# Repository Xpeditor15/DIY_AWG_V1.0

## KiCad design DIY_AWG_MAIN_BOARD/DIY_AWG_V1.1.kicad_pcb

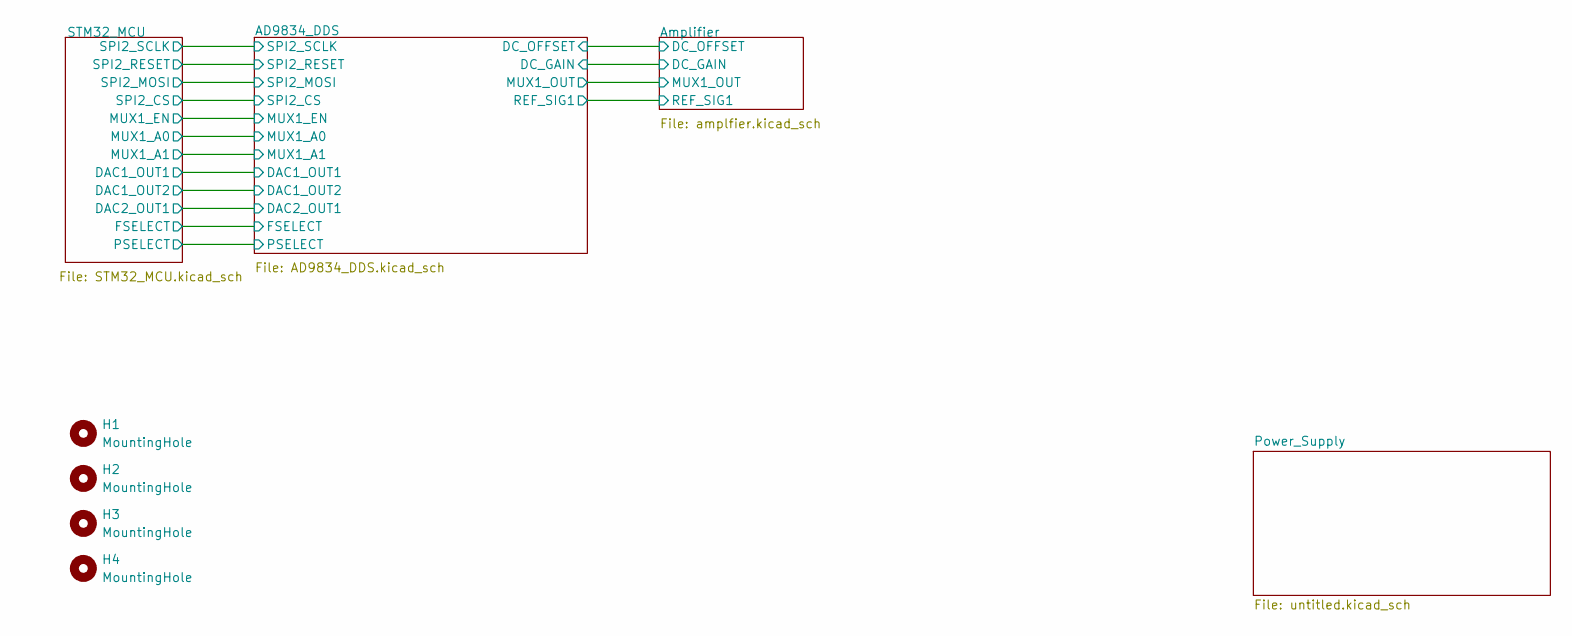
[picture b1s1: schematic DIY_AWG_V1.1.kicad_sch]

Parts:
H1, H2, H3, H4: MountingHole; MountingHole_3.2mm_M3

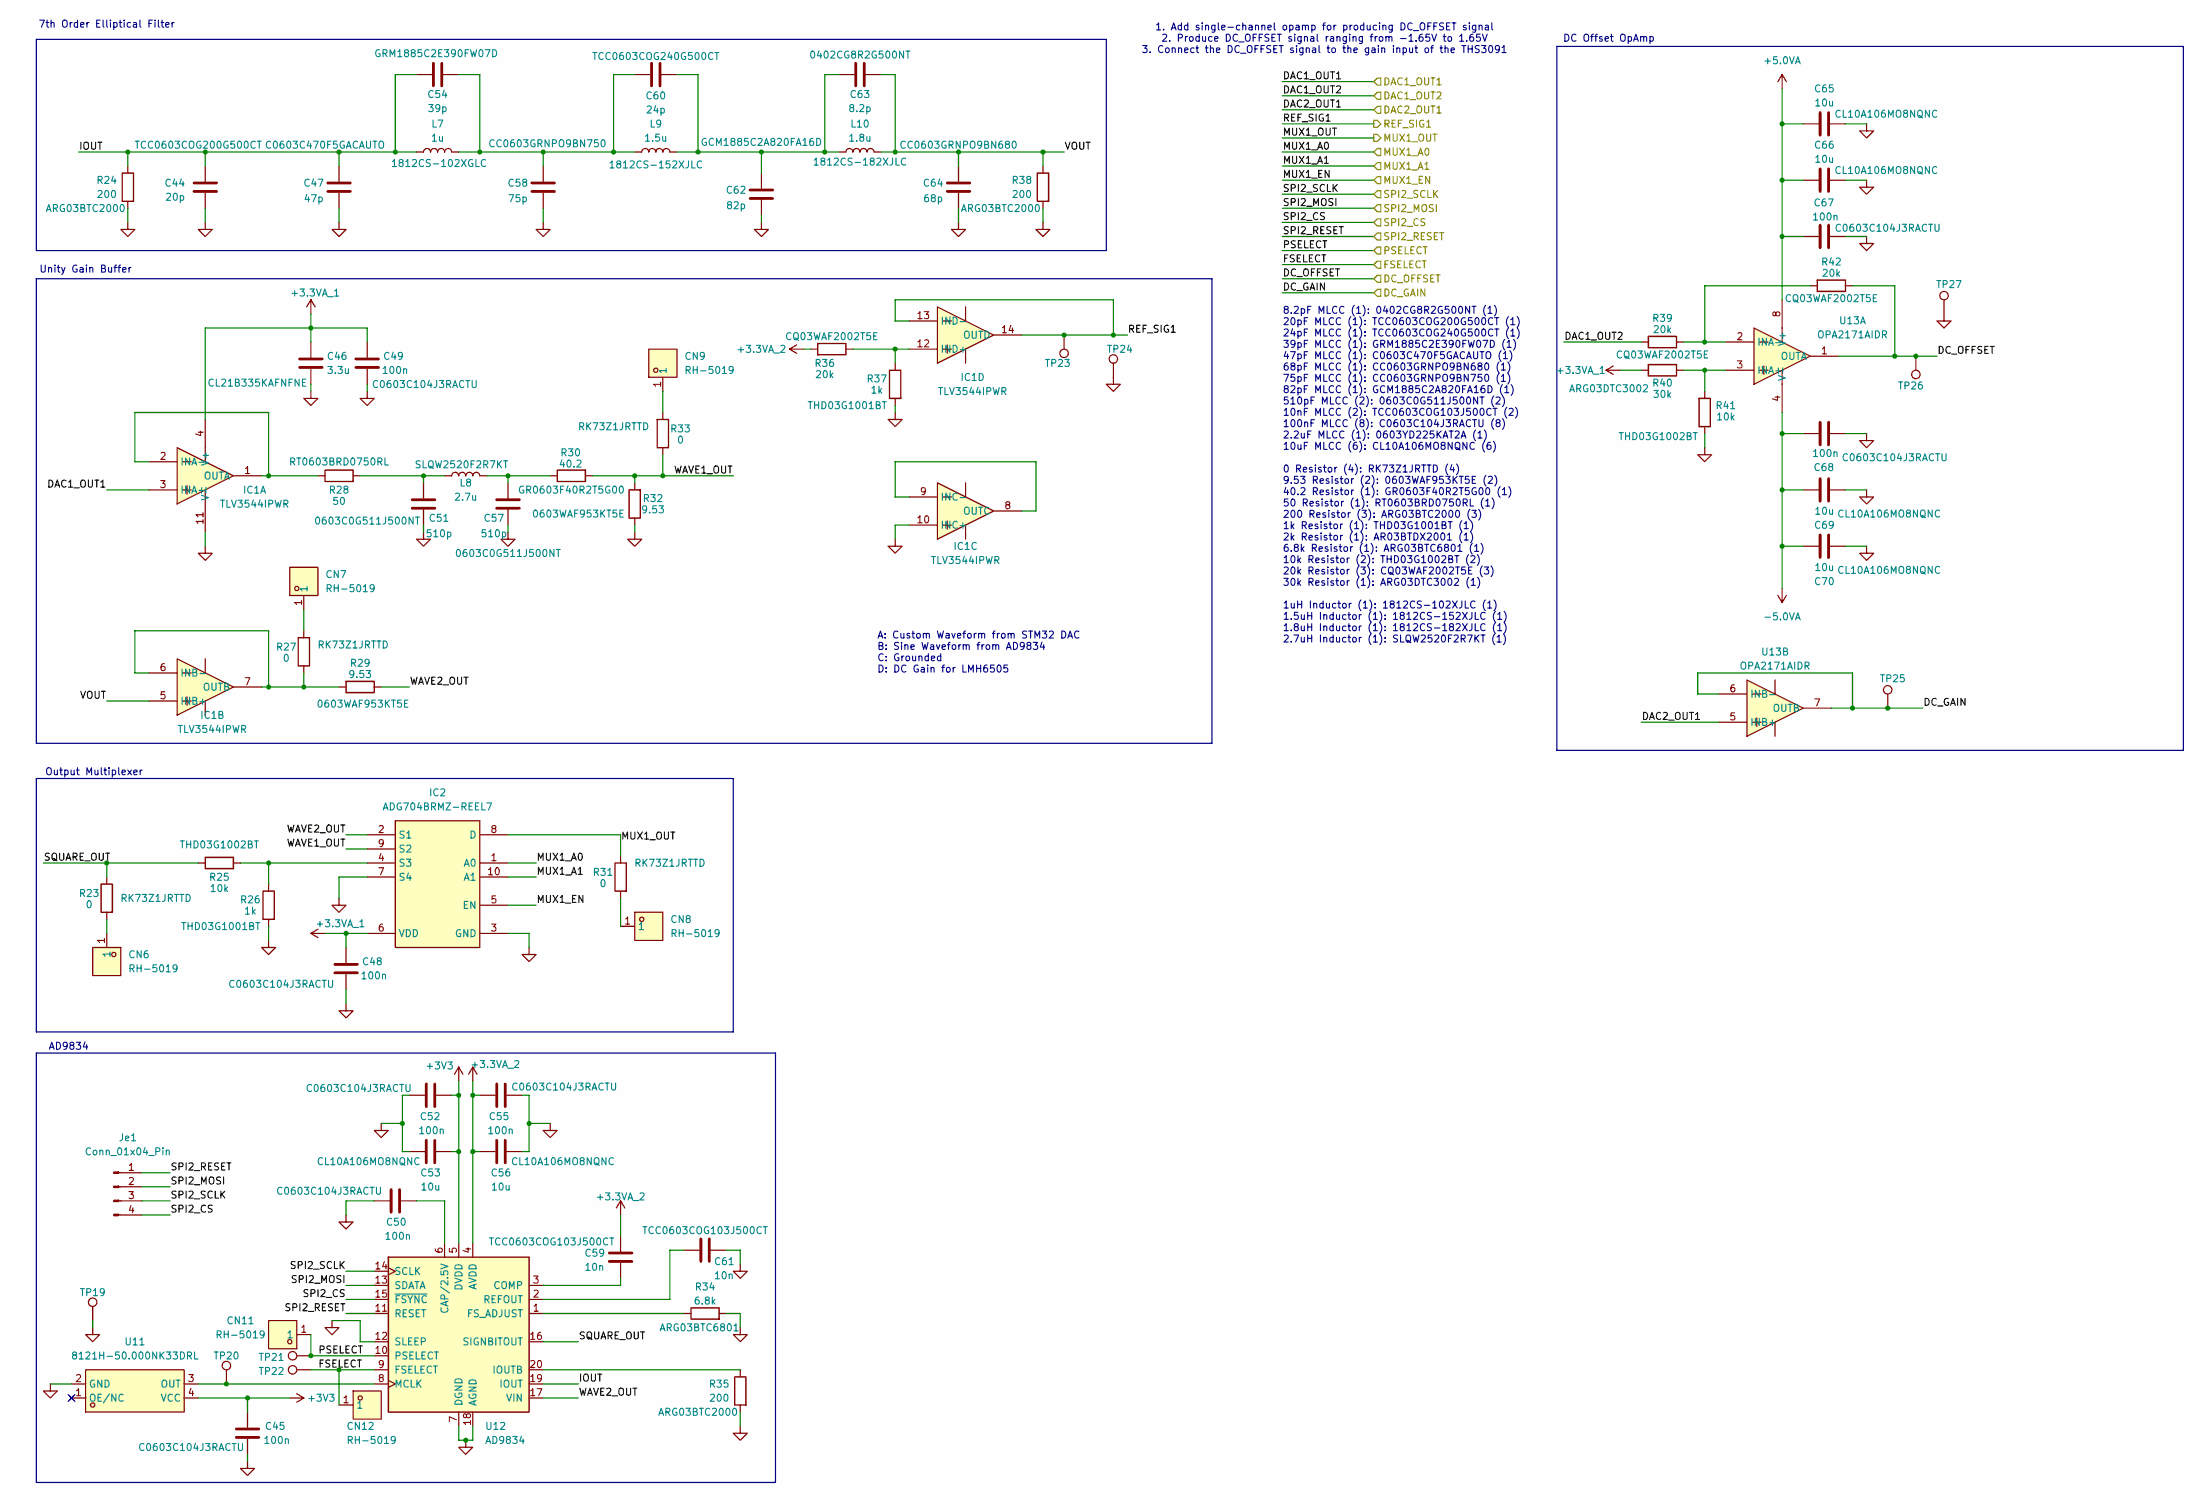
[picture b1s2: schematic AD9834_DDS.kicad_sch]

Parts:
C44: 20p; C_0603_1608Metric; LCSC ID C5360848
C45, C48, C49, C50, C52, C55, C67, C68: 100n; C_0603_1608Metric; LCSC ID C2167388
C46: 3.3u; C_0805_2012Metric; LCSC ID C16194987
C47: 47p; C_0603_1608Metric; LCSC ID C1865294
C51, C57: 510p; C_0603_1608Metric; LCSC ID C49326333
C53, C56, C65, C66, C69, C70: 10u; C_0603_1608Metric; LCSC ID C92487
C54: 39p; C_0603_1608Metric; LCSC ID C22124185
C58: 75p; C_0603_1608Metric; LCSC ID C519466
C59, C61: 10n; C_0603_1608Metric; LCSC ID C7393880
C60: 24p; C_0603_1608Metric; LCSC ID C5375817
C62: 82p; C_0603_1608Metric; LCSC ID C1864236
C63: 8.2p; C_0402_1005Metric; LCSC ID C2857971
C64: 68p; C_0603_1608Metric; LCSC ID C519457
CN6, CN7, CN8, CN9, CN11, CN12: RH-5019; TESTPOINT-SMD_L3.8-W2.0_RH-5019; MPN RH-5019; LCSC Part C5199800
IC1: TLV3544IPWR; TSSOP-14_L5.0-W4.4-P0.65-LS6.4-BL; Manufacturer_Part_Number TLV3544IPWR; Mouser Part Number 595-TLV3544IPWR
IC2: ADG704BRMZ-REEL7; MSOP-10_L3.0-W3.0-P0.50-LS5.0-BL; Manufacturer_Part_Number ADG704BRMZ-REEL7; Mouser Part Number 584-ADG704BRMZ-R7
Je1: Conn_01x04_Pin; PinHeader_1x04_P2.54mm_Vertical
L7: 1u; L_1812_4532Metric; LCSC ID C37639398
L8: 2.7u; L_1008_2520_SLQW2520; LCSC ID C42440934
L9: 1.5u; L_1812_4532Metric; LCSC ID C39924671
L10: 1.8u; L_1812_4532Metric; LCSC ID C38811900
R23, R27, R31, R33: 0; R_0603_1608Metric; LCSC ID C2596815
R24, R35, R38: 200; C_0603_1608Metric; LCSC ID C37635738
R25, R41: 10k; R_0603_1608Metric; LCSC ID C47120023
R26, R37: 1k; R_0603_1608Metric; LCSC ID C52104281
R28: 50; R_0603_1608Metric; LCSC ID C5879483
R29, R32: 9.53; R_0603_1608Metric; LCSC ID C407502
R30: 40.2; R_0603_1608Metric; LCSC ID C49654821
R34: 6.8k; C_0603_1608Metric; LCSC ID C2941290
R36, R39, R42: 20k; R_0603_1608Metric; LCSC ID C2765619
R40: 30k; R_0603_1608Metric; LCSC ID C2758295
TP19, TP20, TP21, TP22, TP23, TP24, TP25, TP26, TP27: TestPoint; TestPoint_Pad_D1.0mm
U11: 8121H-50.000NK33DRL; OSC-SMD_4P-L2.0-W1.6-BL_SIT8008BI-72-33E-54.000000; MPN 8121H-50.000NK33DRL; LCSC Part C46598423
U12: AD9834; TSSOP-20_4.4x6.5mm_P0.65mm
U13: OPA2171AIDR; SOIC-8_L5.0-W4.0-P1.27-LS6.0-BL; MPN OPA2171AIDR; LCSC Part C40904

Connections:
+3.3VA_1: C46.1, C48.1, C49.1, IC1.4 (V+), IC2.6 (VDD), R40.2; also elsewhere on the board
+3.3VA_2: C55.2, C56.2, C59.2, R36.2, U12.4 (AVDD); also elsewhere on the board
+3V3: C45.2, C52.2, C53.2, U11.4 (VCC), U12.5 (DVDD); also elsewhere on the board
+5.0VA: C65.2, C66.2, C67.2, U13.8 (V+); also elsewhere on the board
-5.0VA: C68.2, C69.2, C70.2, U13.4 (V-); also elsewhere on the board
/AD9834_DDS/DAC1_OUT1: IC1.3 (INA+); also elsewhere on the board
/AD9834_DDS/DAC1_OUT2: R39.2; also elsewhere on the board
/AD9834_DDS/DAC2_OUT1: U13.5 (INB+); also elsewhere on the board
/AD9834_DDS/DC_GAIN: TP25.1 (1_1), U13.6 (INB-), U13.7 (OUTB); also elsewhere on the board
/AD9834_DDS/DC_OFFSET: R42.1, TP26.1 (1_1), U13.1 (OUTA); also elsewhere on the board
/AD9834_DDS/FSELECT: CN12.1 (1_1), TP22.1 (1_1), U12.9 (FSELECT); also elsewhere on the board
/AD9834_DDS/IOUT: C44.1, C47.2, C54.1, L7.1, R24.1, U12.19 (IOUT)
/AD9834_DDS/MUX1_A0: IC2.1 (A0); also elsewhere on the board
/AD9834_DDS/MUX1_A1: IC2.10 (A1); also elsewhere on the board
/AD9834_DDS/MUX1_EN: IC2.5 (EN); also elsewhere on the board
/AD9834_DDS/MUX1_OUT: IC2.8 (D), R31.1; also elsewhere on the board
/AD9834_DDS/PSELECT: CN11.1 (1_1), TP21.1 (1_1), U12.10 (PSELECT); also elsewhere on the board
/AD9834_DDS/REF_SIG1: IC1.13 (IND-), IC1.14 (OUTD), TP23.1 (1_1); also elsewhere on the board
/AD9834_DDS/SPI2_CS: Je1.4, U12.15 (~FSYNC); also elsewhere on the board
/AD9834_DDS/SPI2_MOSI: Je1.2, U12.13 (SDATA); also elsewhere on the board
/AD9834_DDS/SPI2_RESET: Je1.1, U12.11 (RESET); also elsewhere on the board
/AD9834_DDS/SPI2_SCLK: Je1.3, U12.14 (SCLK); also elsewhere on the board
/AD9834_DDS/SQUARE_OUT: R23.1, R25.1, U12.16 (SIGNBITOUT)
/AD9834_DDS/VOUT: C63.2, C64.2, IC1.5 (INB+), L10.2, R38.1
/AD9834_DDS/WAVE1_OUT: IC2.9 (S2), R30.2, R32.2, R33.1
/AD9834_DDS/WAVE2_OUT: IC2.2 (S1), R29.1, U12.17 (VIN)
GND: C44.2, C45.1, C46.2, C47.1, C48.2, C49.2, C50.1, C51.1, C52.1, C53.1, C55.1, C56.1, C57.1, C58.1, C61.1, C62.1, C64.1, C65.1, C66.1, C67.1, C68.1, C69.1, C70.1, IC1.10 (INC+), IC1.11 (V-), IC2.3 (GND), IC2.7 (S4), R24.2, R26.2, R32.1, R34.2, R35.2, R37.2, R38.2, R41.1, TP19.1 (1_1), TP24.1 (1_1), TP27.1 (1_1), U11.2 (GND), U12.7 (DGND), U12.12 (SLEEP), U12.18 (AGND); also elsewhere on the board
unnamed: C51.2, L8.2, R28.2
unnamed: C54.2, C58.2, C60.1, L7.2, L9.1
unnamed: C57.2, L8.1, R30.1
unnamed: C60.2, C62.2, C63.1, L9.2, L10.1
unnamed: CN6.1 (1_1), R23.2
unnamed: CN7.1 (1_1), R27.2
unnamed: CN8.1 (1_1), R31.2
unnamed: CN9.1 (1_1), R33.2
unnamed: IC1.1 (OUTA), IC1.2 (INA-), R28.1
unnamed: IC1.6 (INB-), IC1.7 (OUTB), R27.1, R29.2
unnamed: IC1.8 (OUTC), IC1.9 (INC-)
unnamed: IC1.12 (IND+), R36.1, R37.1
unnamed: IC2.4 (S3), R25.2, R26.1
unnamed: TP20.1 (1_1), U11.3 (OUT), U12.8 (MCLK)
unnamed: C50.2, U12.6 (CAP/2.5V)
unnamed: C59.1, U12.3 (COMP)
unnamed: R34.1, U12.1 (FS_ADJUST)
unnamed: R35.1, U12.20 (IOUTB)
unnamed: C61.2, U12.2 (REFOUT)
unnamed: R40.1, R41.2, U13.3 (INA+)
unnamed: R39.1, R42.2, U13.2 (INA-)

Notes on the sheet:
DC Offset OpAmp
AD9834
Unity Gain Buffer
Output Multiplexer
8.2pF MLCC (1): 0402CG8R2G500NT (1) 20pF MLCC (1): TCC0603COG200G500CT (1) 24pF MLCC (1): TCC0603COG240G500CT (1) 39pF MLCC (1): GRM1885C2E390FW07D (1) 47pF MLCC (1): C0603C470F5GACAUTO (1) 68pF MLCC (1): CC0603GRNPO9BN680 (1) 75pF MLCC (1): CC0603GRNPO9BN750 (1) 82pF MLCC (1): GCM1885C2A820FA16D (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
7th Order Elliptical Filter
A: Custom Waveform from STM32 DAC B: Sine Waveform from AD9834 C: Grounded D: DC Gain for LMH6505
1. Add single-channel opamp for producing DC_OFFSET signal 2. Produce DC_OFFSET signal ranging from -1.65V to 1.65V 3. Connect the DC_OFFSET signal to the gain input of the THS3091

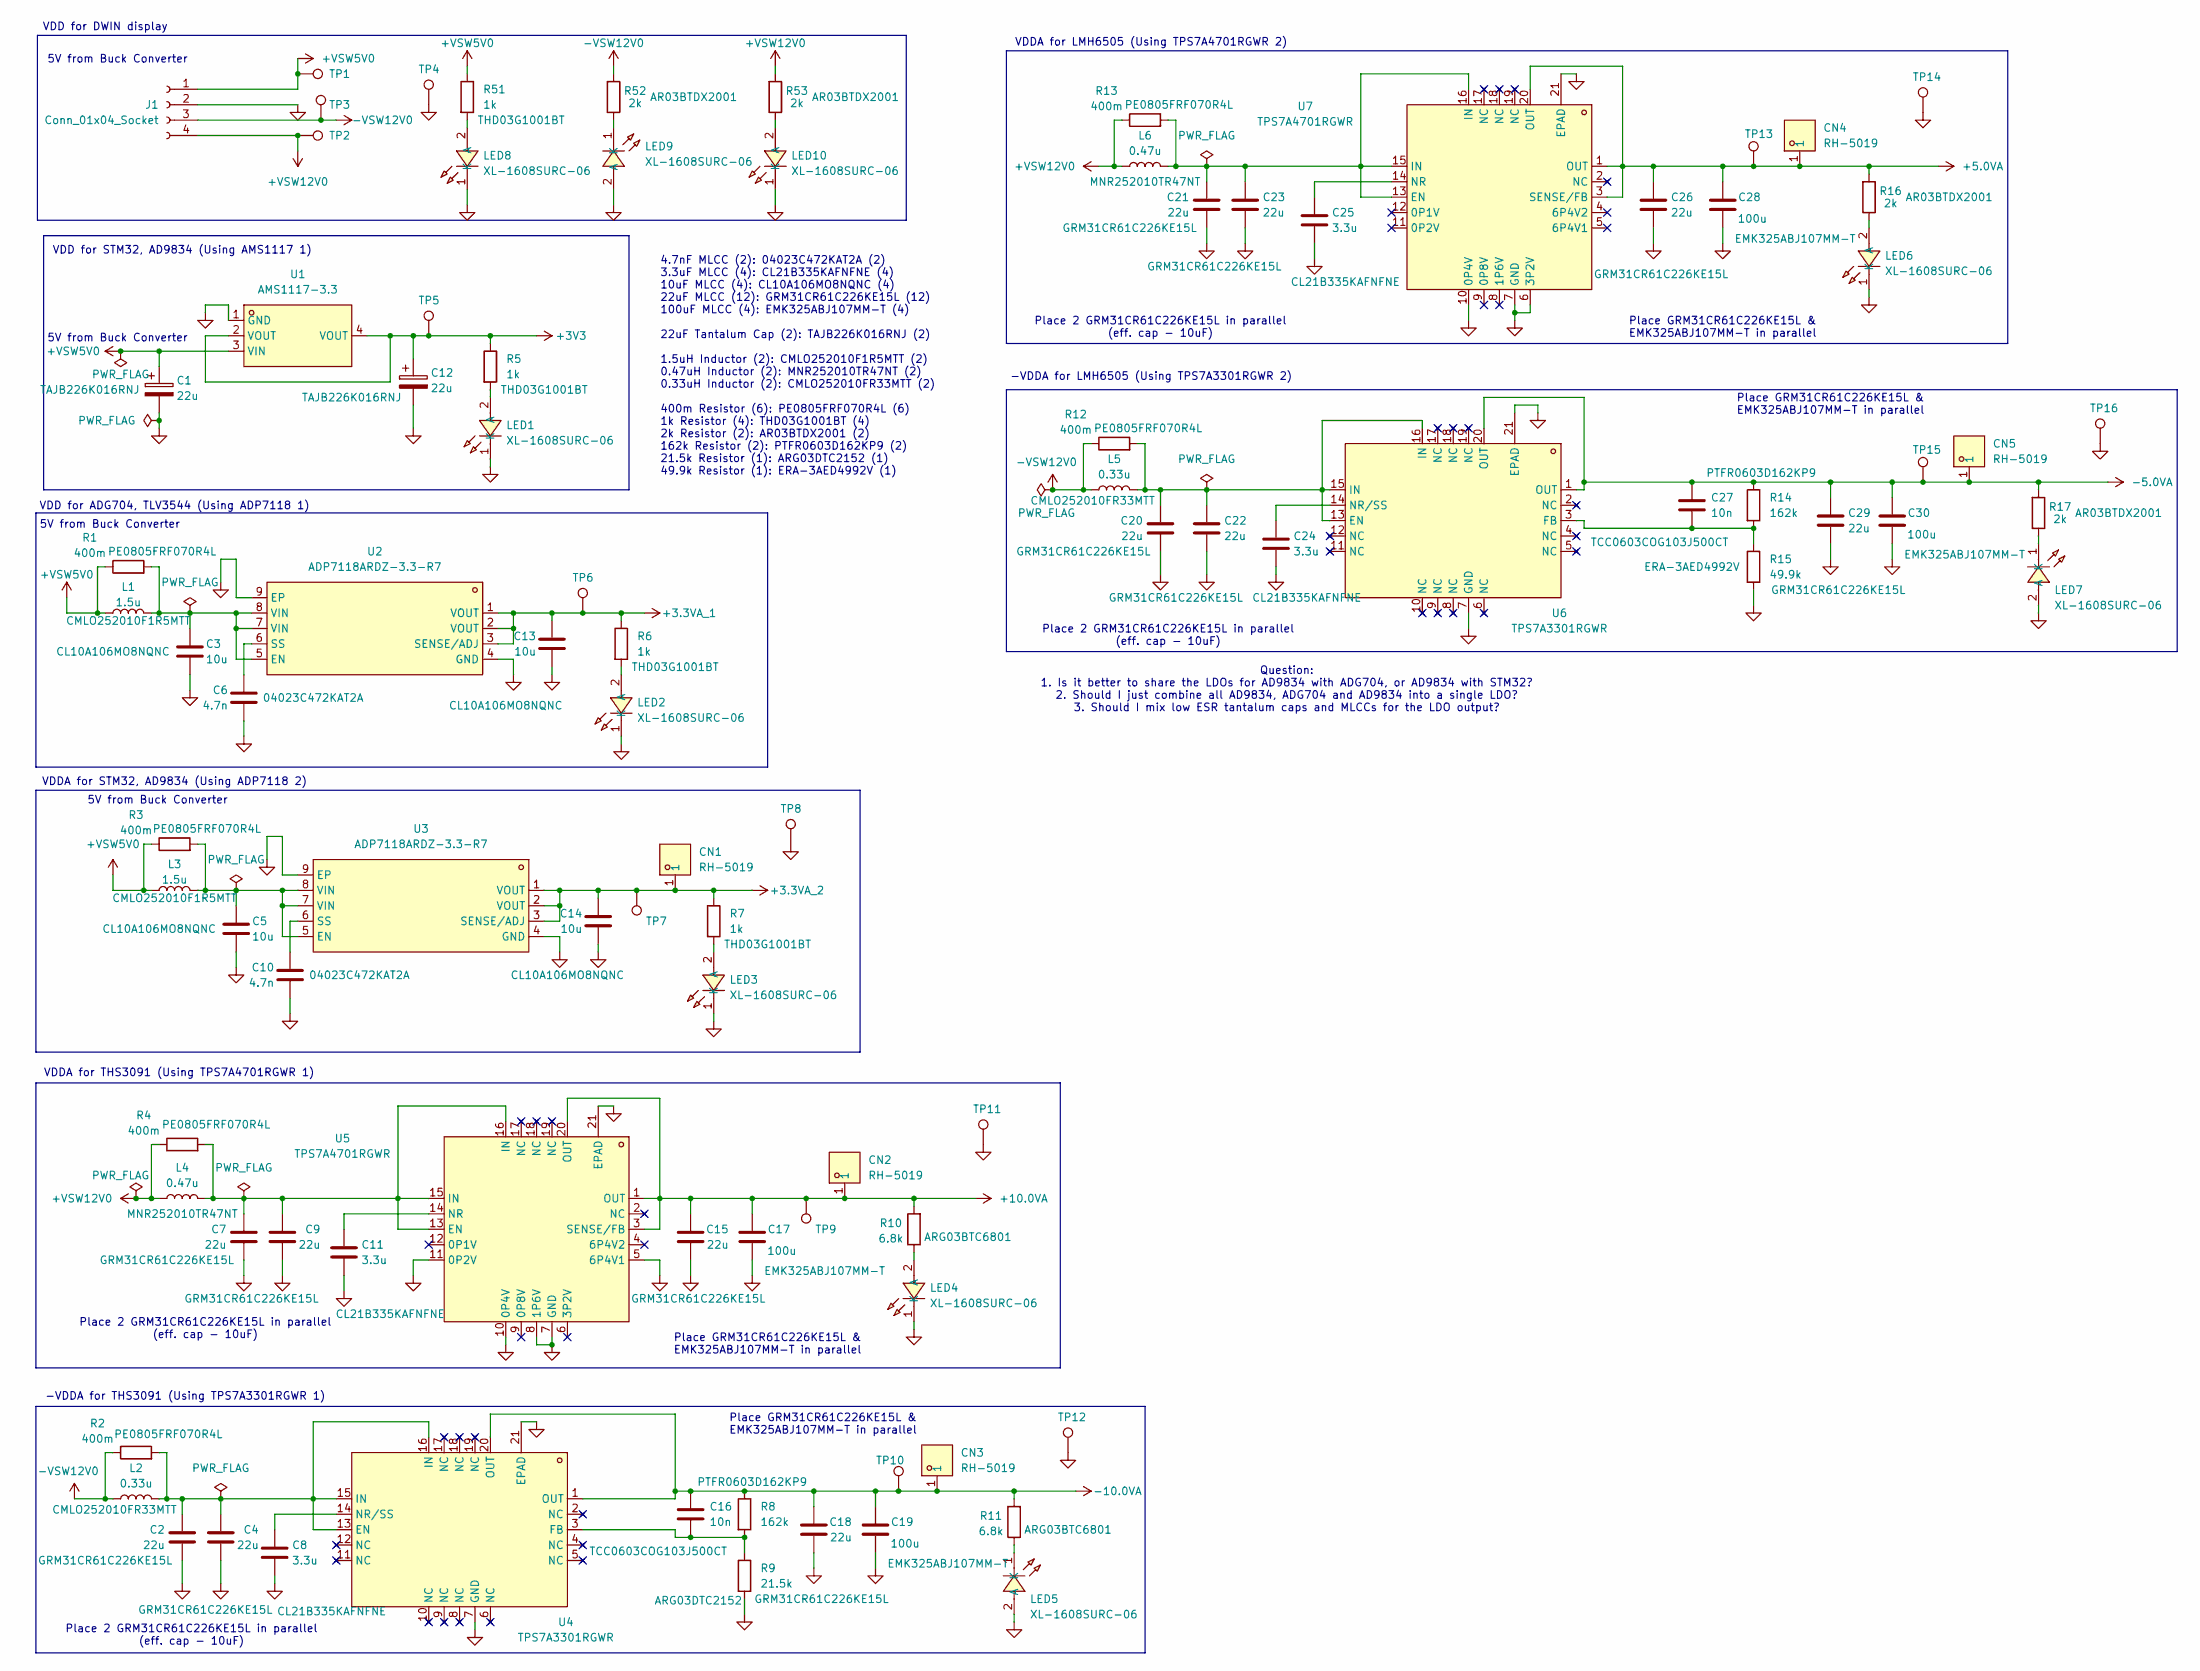
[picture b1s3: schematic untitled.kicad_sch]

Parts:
C1: 22u; CASE-B_3528; LCSC ID: C8020
C2, C4, C7, C9, C15, C18, C20, C21, C22, C23, C26, C29: 22u; C_1206_3216Metric; LCSC ID C77088
C3, C5, C13, C14: 10u; C_0603_1608Metric; LCSC ID C92487
C6, C10: 4.7n; C_0402_1005Metric
C8, C11, C24, C25: 3.3u; C_0805_2012Metric; LCSC ID C16194987
C12: 22u; CASE-B_3528
C16, C27: 10n; C_0603_1608Metric; LCSC ID C7393880
C17, C19, C28, C30: 100u; C_1210_3225Metric; LCSC ID C77088
CN1, CN2, CN3, CN4, CN5: RH-5019; TESTPOINT-SMD_L3.8-W2.0_RH-5019; MPN RH-5019; LCSC Part C5199800
J1: Conn_01x04_Socket; JST_XH_B4B-XH-A_1x04_P2.50mm_Vertical
L1, L3: 1.5u; L_1008_2520Metric; LCSC ID C438917
L2, L5: 0.33u; L_1008_2520Metric; LCSC ID C438913
L4, L6: 0.47u; L_1008_2520Metric; LCSC ID C18221969
LED1, LED2, LED3, LED4, LED5, LED6, LED7, LED8, LED9, LED10: XL-1608SURC-06; LED0603-RD_RED; MPN XL-1608SURC-06; LCSC Part C965799
R1, R2, R3, R4, R12, R13: 400m; R_0805_2012Metric; LCSC ID C7261230
R5, R6, R7, R51: 1k; R_0603_1608Metric; LCSC ID C52104281
R8, R14: 162k; R_0603_1608Metric; LCSC ID C47116096
R9: 21.5k; R_0603_1608Metric; LCSC ID C311891
R10, R11: 6.8k; C_0603_1608Metric; LCSC ID C2941290
R15: 49.9k; R_0603_1608Metric; LCSC ID C2074281
R16, R17, R52, R53: 2k; R_0603_1608Metric; LCSC ID C319701
TP1, TP2, TP3, TP4, TP5, TP6, TP7, TP8, TP9, TP10, TP11, TP12, TP13, TP14, TP15, TP16: TestPoint; TestPoint_Pad_D1.0mm
U1: AMS1117-3.3; SOT-223-3_L6.5-W3.4-P2.30-LS7.0-BR; MPN AMS1117-3.3; LCSC Part C6186
U2, U3: ADP7118ARDZ-3.3-R7; SOIC-8_L4.9-W3.9-P1.27-LS6.0-BL-EP2.3; MPN ADP7118ARDZ-3.3-R7; LCSC Part C153731
U4, U6: TPS7A3301RGWR; VQFN-20_L5.0-W5.0-P0.65-TL-EP; MPN TPS7A3301RGWR; LCSC Part C90082
U5, U7: TPS7A4701RGWR; VQFN-20_L5.0-W5.0-P0.65-TL-EP; MPN TPS7A4701RGWR; LCSC Part C90084

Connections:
+3.3VA_1: C13.1, R6.1, TP6.1 (1_1), U2.1 (VOUT), U2.2 (VOUT), U2.3 (SENSE/ADJ); also elsewhere on the board
+3.3VA_2: C14.1, CN1.1 (1_1), R7.1, TP7.1 (1_1), U3.1 (VOUT), U3.2 (VOUT), U3.3 (SENSE/ADJ); also elsewhere on the board
+3V3: C12.1, R5.1, TP5.1 (1_1), U1.2 (VOUT), U1.4 (VOUT); also elsewhere on the board
+5.0VA: C26.1, C28.1, CN4.1 (1_1), R16.2, TP13.1 (1_1), U7.1 (OUT), U7.3 (SENSE/FB), U7.20 (OUT); also elsewhere on the board
+10.0VA: C15.1, C17.1, CN2.1 (1_1), R10.2, TP9.1 (1_1), U5.1 (OUT), U5.3 (SENSE/FB), U5.20 (OUT); also elsewhere on the board
+VSW5V0: C1.1, J1.1, L1.1, L3.1, R1.1, R3.1, R51.1, TP1.1 (1_1), U1.3 (VIN); also elsewhere on the board
+VSW12V0: J1.4, L4.1, L6.1, R4.1, R13.1, R53.2, TP2.1 (1_1)
-5.0VA: C27.1, C29.1, C30.1, CN5.1 (1_1), R14.1, R17.2, TP15.1 (1_1), U6.1 (OUT), U6.20 (OUT); also elsewhere on the board
-10.0VA: C16.1, C18.1, C19.1, CN3.1 (1_1), R8.1, R11.2, TP10.1 (1_1), U4.1 (OUT), U4.20 (OUT); also elsewhere on the board
-VSW12V0: J1.3, L2.1, L5.1, R2.1, R12.1, R52.2, TP3.1 (1_1)
GND: C1.2, C2.2, C3.2, C4.2, C5.2, C6.2, C7.2, C8.2, C9.2, C10.2, C11.2, C12.2, C13.2, C14.2, C15.2, C17.2, C18.2, C19.2, C20.2, C21.2, C22.2, C23.2, C24.2, C25.2, C26.2, C28.2, C29.2, C30.2, J1.2, LED1.1 (K), LED2.1 (K), LED3.1 (K), LED4.1 (K), LED5.2 (A), LED6.1 (K), LED7.2 (A), LED8.1 (K), LED9.2 (A), LED10.1 (K), R9.2, R15.2, TP4.1 (1_1), TP8.1 (1_1), TP11.1 (1_1), TP12.1 (1_1), TP14.1 (1_1), TP16.1 (1_1), U1.1 (GND), U2.4 (GND), U2.9 (EP), U3.4 (GND), U3.9 (EP), U4.7 (GND), U4.21 (EPAD), U5.5 (6P4V1), U5.7 (GND), U5.8 (1P6V), U5.10 (0P4V), U5.11 (0P2V), U5.21 (EPAD), U6.7 (GND), U6.21 (EPAD), U7.6 (3P2V), U7.7 (GND), U7.10 (0P4V), U7.21 (EPAD); also elsewhere on the board
unnamed: LED1.2 (A), R5.2
unnamed: LED2.2 (A), R6.2
unnamed: LED3.2 (A), R7.2
unnamed: LED4.2 (A), R10.1
unnamed: LED5.1 (K), R11.1
unnamed: LED6.2 (A), R16.1
unnamed: LED7.1 (K), R17.1
unnamed: LED8.2 (A), R51.2
unnamed: LED9.1 (K), R52.1
unnamed: LED10.2 (A), R53.1
unnamed: C3.1, L1.2, R1.2, U2.5 (EN), U2.7 (VIN), U2.8 (VIN)
unnamed: C6.1, U2.6 (SS)
unnamed: C5.1, L3.2, R3.2, U3.5 (EN), U3.7 (VIN), U3.8 (VIN)
unnamed: C10.1, U3.6 (SS)
unnamed: C2.1, C4.1, L2.2, R2.2, U4.13 (EN), U4.15 (IN), U4.16 (IN)
unnamed: C16.2, R8.2, R9.1, U4.3 (FB)
unnamed: C8.1, U4.14 (NR/SS)
unnamed: C7.1, C9.1, L4.2, R4.2, U5.13 (EN), U5.15 (IN), U5.16 (IN)
unnamed: C11.1, U5.14 (NR)
unnamed: C20.1, C22.1, L5.2, R12.2, U6.13 (EN), U6.15 (IN), U6.16 (IN)
unnamed: C27.2, R14.2, R15.1, U6.3 (FB)
unnamed: C24.1, U6.14 (NR/SS)
unnamed: C21.1, C23.1, L6.2, R13.2, U7.13 (EN), U7.15 (IN), U7.16 (IN)
unnamed: C25.1, U7.14 (NR)

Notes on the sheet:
4.7nF MLCC (2): 04023C472KAT2A (2) 3.3uF MLCC (4): CL21B335KAFNFNE (4) 10uF MLCC (4): CL10A106MO8NQNC (4) 22uF MLCC (12): GRM31CR61C226KE15L (12) 100uF MLCC (4): EMK325ABJ107MM-T (4) 22uF Tantalum Cap (2): TAJB226K016RNJ (2) 1.5uH Inductor (2): CMLO252010F1R5MTT (2) 0.47uH Inductor (2): MNR252010TR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
Place 2 GRM31CR61C226KE15L in parallel (eff. cap - 10uF)
Place GRM31CR61C226KE15L & EMK325ABJ107MM-T in parallel
5V from Buck Converter
VDDA for STM32, AD9834 (Using ADP7118 2)
-VDDA for LMH6505 (Using TPS7A3301RGWR 2)
VDDA for THS3091 (Using TPS7A4701RGWR 1)
VDD for ADG704, TLV3544 (Using ADP7118 1)
VDD for DWIN display
Question: 1. Is it better to share the LDOs for AD9834 with ADG704, or AD9834 with STM32? 2. Should I just combine all AD9834, ADG704 and AD9834 into a single LDO? 3. Should I mix low ESR tantalum caps and MLCCs for the LDO output?
VDD for STM32, AD9834 (Using AMS1117 1)
VDDA for LMH6505 (Using TPS7A4701RGWR 2)
-VDDA for THS3091 (Using TPS7A3301RGWR 1)

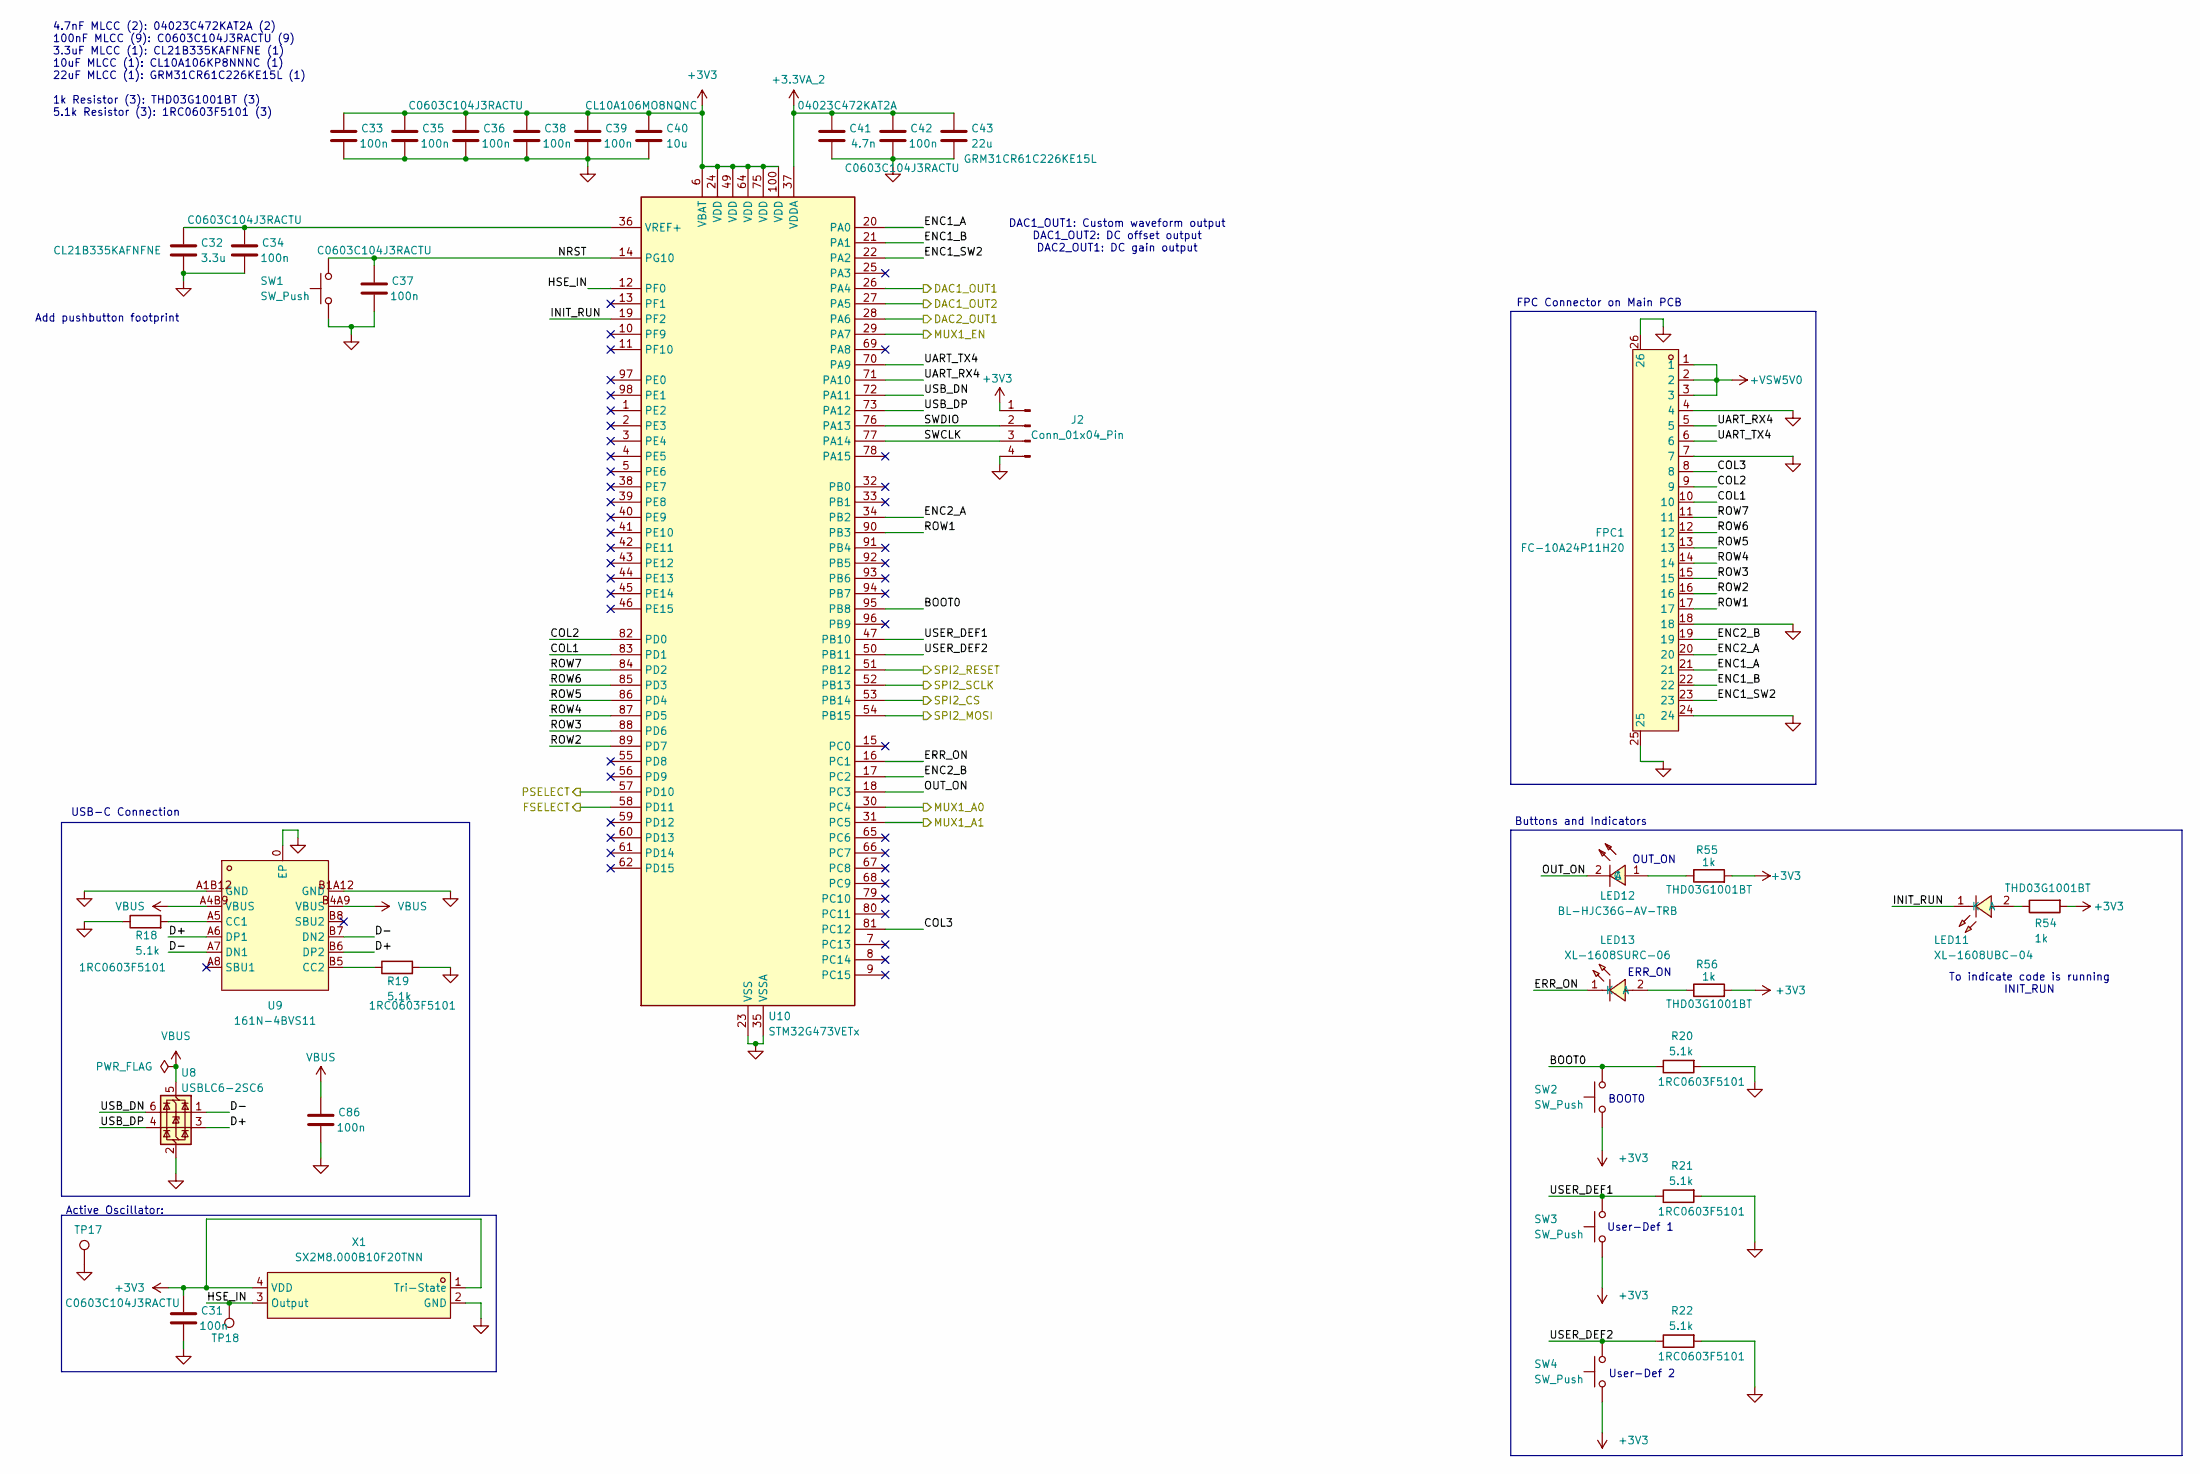
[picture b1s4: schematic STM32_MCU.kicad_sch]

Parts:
C31, C33, C34, C35, C36, C37, C38, C39, C42, C86: 100n; C_0603_1608Metric; LCSC ID C2167388
C32: 3.3u; C_0805_2012Metric; LCSC ID C16194987
C40: 10u; C_0603_1608Metric; LCSC ID C92487
C41: 4.7n; C_0402_1005Metric; LCSC ID C5128374
C43: 22u; C_1206_3216Metric; LCSC ID C77088
FPC1: FC-10A24P11H20; FPC-SMD_24P-P1.00_FC-10A24P11H20; MPN FC-10A24P11H20; LCSC Part C23397378
J2: Conn_01x04_Pin; PinHeader_1x04_P2.54mm_Vertical
LED11: XL-1608UBC-04; LED0603-RD_BLUE; MPN XL-1608UBC-04; LCSC Part C965807
LED12: BL-HJC36G-AV-TRB; LED0603-R-RD_AMBER; MPN BL-HJC36G-AV-TRB; LCSC Part C165983
LED13: XL-1608SURC-06; LED0603-RD_RED; MPN XL-1608SURC-06; LCSC Part C965799
R18, R19, R20, R21, R22: 5.1k; R_0603_1608Metric; LCSC ID C53224208
R54, R55, R56: 1k; R_0603_1608Metric; LCSC ID C52104281
SW1, SW2, SW3, SW4: SW_Push; SW-SMD_L6.1-W3.5-LS8.6; LCSC ID C51978298
TP17, TP18: TestPoint; TestPoint_Pad_D1.0mm
U8: USBLC6-2SC6; SOT-23-6
U9: 161N-4BVS11; USB-C-SMD_HANELECTRICITY_161N-4XVS11; MPN 161N-4BVS11; LCSC Part C5440752
U10: STM32G473VETx; LQFP-100_14x14mm_P0.5mm
X1: SX2M8.000B10F20TNN; OSC-SMD_4P-L2.5-W2.0-BL; MPN SX2M8.000B10F20TNN; LCSC Part C7431260

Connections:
+3.3VA_2: C41.1, C42.1, C43.1, U10.37 (VDDA); also elsewhere on the board
+3V3: C31.1, C33.1, C35.1, C36.1, C38.1, C39.1, C40.1, J2.1, R54.2, R55.2, R56.2, SW2.1, SW3.1, SW4.1, U10.6 (VBAT), U10.24 (VDD), U10.49 (VDD), U10.64 (VDD), U10.75 (VDD), U10.100 (VDD), X1.1 (Tri-State), X1.4 (VDD); also elsewhere on the board
+VSW5V0: FPC1.1, FPC1.2, FPC1.3; also elsewhere on the board
/AD9834_DDS/DAC1_OUT1: U10.26 (PA4); also elsewhere on the board
/AD9834_DDS/DAC1_OUT2: U10.27 (PA5); also elsewhere on the board
/AD9834_DDS/DAC2_OUT1: U10.28 (PA6); also elsewhere on the board
/AD9834_DDS/FSELECT: U10.58 (PD11); also elsewhere on the board
/AD9834_DDS/MUX1_A0: U10.30 (PC4); also elsewhere on the board
/AD9834_DDS/MUX1_A1: U10.31 (PC5); also elsewhere on the board
/AD9834_DDS/MUX1_EN: U10.29 (PA7); also elsewhere on the board
/AD9834_DDS/PSELECT: U10.57 (PD10); also elsewhere on the board
/AD9834_DDS/SPI2_CS: U10.53 (PB14); also elsewhere on the board
/AD9834_DDS/SPI2_MOSI: U10.54 (PB15); also elsewhere on the board
/AD9834_DDS/SPI2_RESET: U10.51 (PB12); also elsewhere on the board
/AD9834_DDS/SPI2_SCLK: U10.52 (PB13); also elsewhere on the board
/STM32_MCU/BOOT0: R20.1, SW2.2, U10.95 (PB8)
/STM32_MCU/COL1: FPC1.10, U10.83 (PD1)
/STM32_MCU/COL2: FPC1.9, U10.82 (PD0)
/STM32_MCU/COL3: FPC1.8, U10.81 (PC12)
/STM32_MCU/D+: U8.3 (I/O2), U9.A6 (DP1), U9.B6 (DP2)
/STM32_MCU/D-: U8.1 (I/O1), U9.A7 (DN1), U9.B7 (DN2)
/STM32_MCU/ENC1_A: FPC1.21, U10.20 (PA0)
/STM32_MCU/ENC1_B: FPC1.22, U10.21 (PA1)
/STM32_MCU/ENC1_SW2: FPC1.23, U10.22 (PA2)
/STM32_MCU/ENC2_A: FPC1.20, U10.34 (PB2)
/STM32_MCU/ENC2_B: FPC1.19, U10.17 (PC2)
/STM32_MCU/ERR_ON: LED13.1 (K), U10.16 (PC1)
/STM32_MCU/HSE_IN: TP18.1 (1_1), U10.12 (PF0), X1.3 (Output)
/STM32_MCU/INIT_RUN: LED11.1 (K), U10.19 (PF2)
/STM32_MCU/NRST: C37.1, SW1.2, U10.14 (PG10)
/STM32_MCU/OUT_ON: LED12.2 (C), U10.18 (PC3)
/STM32_MCU/ROW1: FPC1.17, U10.90 (PB3)
/STM32_MCU/ROW2: FPC1.16, U10.89 (PD7)
/STM32_MCU/ROW3: FPC1.15, U10.88 (PD6)
/STM32_MCU/ROW4: FPC1.14, U10.87 (PD5)
/STM32_MCU/ROW5: FPC1.13, U10.86 (PD4)
/STM32_MCU/ROW6: FPC1.12, U10.85 (PD3)
/STM32_MCU/ROW7: FPC1.11, U10.84 (PD2)
/STM32_MCU/SWCLK: J2.3, U10.77 (PA14)
/STM32_MCU/SWDIO: J2.2, U10.76 (PA13)
/STM32_MCU/UART_RX4: FPC1.5, U10.71 (PA10)
/STM32_MCU/UART_TX4: FPC1.6, U10.70 (PA9)
/STM32_MCU/USB_DN: U8.6 (I/O1), U10.72 (PA11)
/STM32_MCU/USB_DP: U8.4 (I/O2), U10.73 (PA12)
/STM32_MCU/USER_DEF1: R21.1, SW3.2, U10.47 (PB10)
/STM32_MCU/USER_DEF2: R22.1, SW4.2, U10.50 (PB11)
GND: C31.2, C32.2, C33.2, C34.2, C35.2, C36.2, C37.2, C38.2, C39.2, C40.2, C41.2, C42.2, C43.2, C86.2, FPC1.4, FPC1.7, FPC1.18, FPC1.24, FPC1.25, FPC1.26, J2.4, R18.1, R19.2, R20.2, R21.2, R22.2, SW1.1, TP17.1 (1_1), U8.2 (GND), U9.0 (EP), U9.A1B12 (GND), U9.B1A12 (GND), U10.23 (VSS), U10.35 (VSSA), U10.48 (VSS), U10.63 (VSS), U10.74 (VSS), U10.99 (VSS), X1.2 (GND); also elsewhere on the board
unnamed: LED11.2 (A), R54.1
unnamed: LED12.1 (A), R55.1
unnamed: LED13.2 (A), R56.1
unnamed: R18.2, U9.A5 (CC1)
unnamed: R19.1, U9.B5 (CC2)
unnamed: C32.1, C34.1, U10.36 (VREF+)
VBUS: C86.1, U8.5 (VBUS), U9.A4B9 (VBUS), U9.B4A9 (VBUS)

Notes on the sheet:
Active Oscillator:
BOOT0
OUT_ON
User-Def 2
Add pushbutton footprint
ERR_ON
4.7nF MLCC (2): 04023C472KAT2A (2) 100nF MLCC (9): C0603C104J3RACTU (9) 3.3uF MLCC (1): CL21B335KAFNFNE (1) 10uF MLCC (1): CL10A106KP8NNNC (1) 22uF MLCC (1): GRM31CR61C226KE15L (1) 1k Resistor (3): THD03G1001BT (3) 5.1k Resistor (3): 1RC0603F5101 (3)
User-Def 1
Buttons and Indicators
DAC1_OUT1: Custom waveform output DAC1_OUT2: DC offset output DAC2_OUT1: DC gain output
FPC Connector on Main PCB
USB-C Connection
To indicate code is running INIT_RUN
